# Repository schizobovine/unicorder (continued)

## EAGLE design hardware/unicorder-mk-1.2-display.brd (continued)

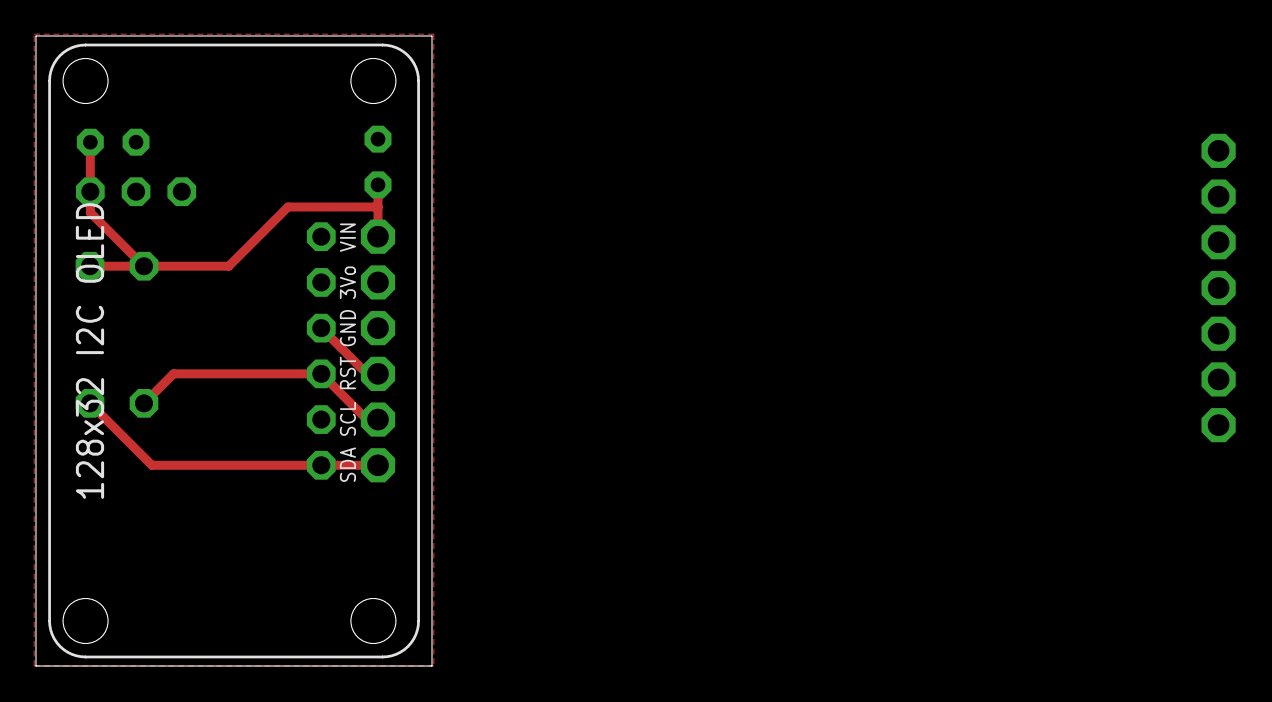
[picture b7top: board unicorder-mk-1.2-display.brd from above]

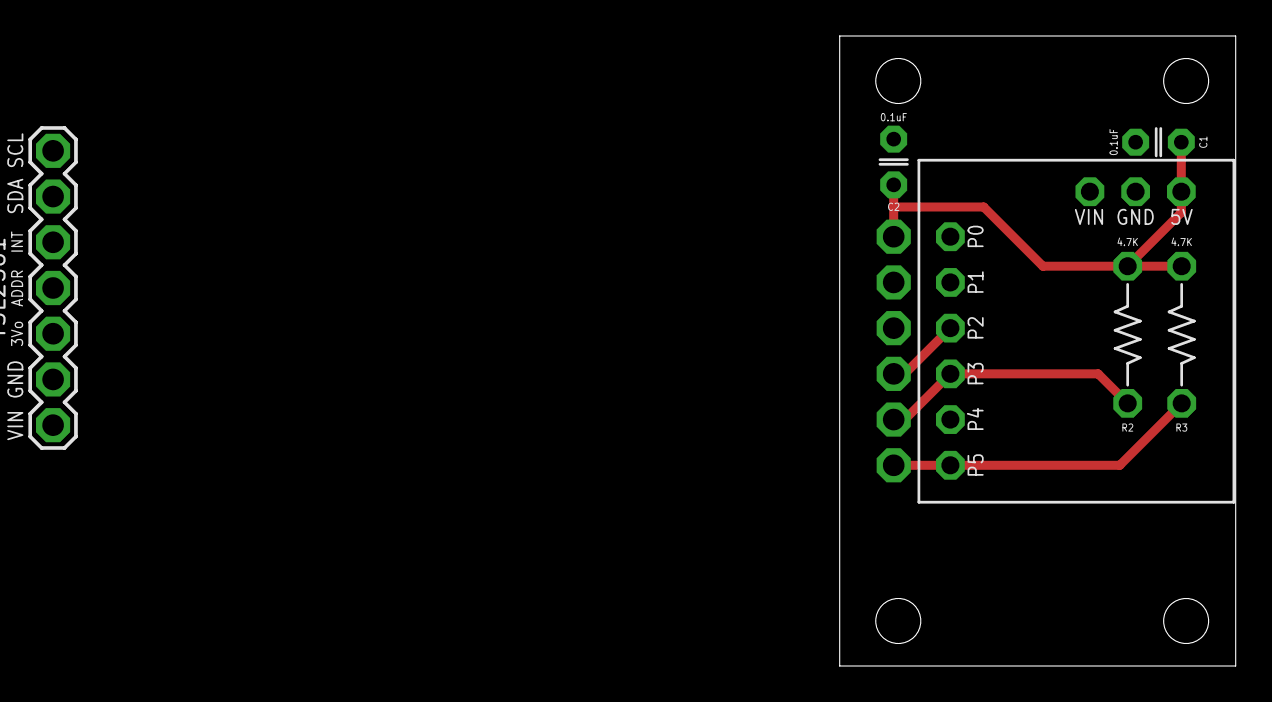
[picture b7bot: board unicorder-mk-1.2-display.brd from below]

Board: 2 copper layers, 22.0 x 35.0 mm, 8 parts (6 on the bottom side), 5 nets.

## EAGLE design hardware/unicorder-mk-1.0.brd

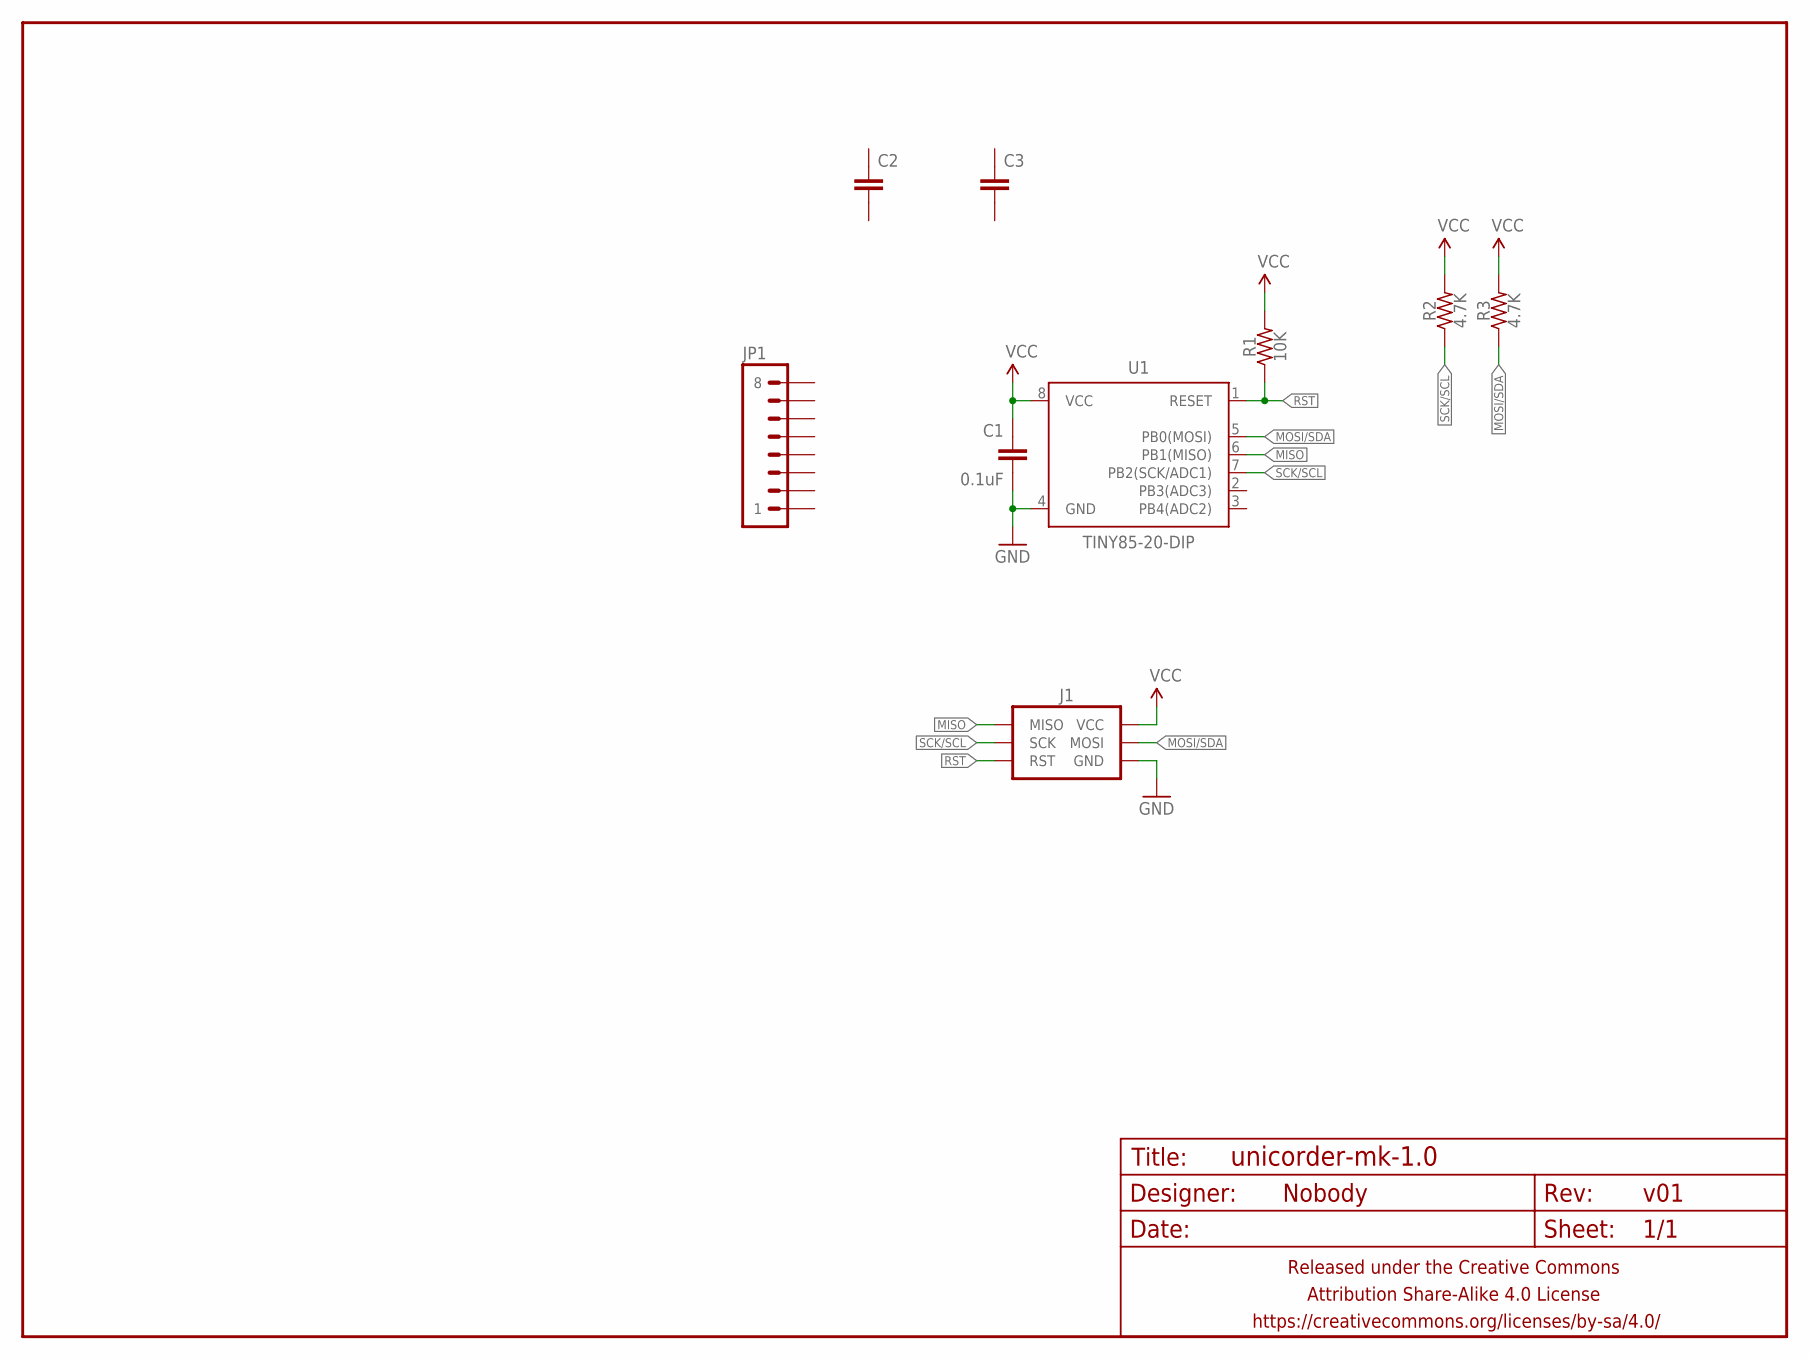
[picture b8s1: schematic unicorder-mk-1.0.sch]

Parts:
C1: 0.1uF; C025-024X044
C2, C3: CAPACITOR-CERAMIC025-024X044; C025-024X044
FRAME1: FRAME-LETTERNO_PACKAGE; DUMMY
J1: AVR_SPI_PRG_6PTH; 2X3
JP1: M081X08; 1X08
R1: 10K; RESISTOR-AXIAL-PTH-5.08MM
R2, R3: 4.7K; RESISTOR-AXIAL-PTH-5.08MM
U1: TINY85-20-DIP; DIP08

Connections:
GND: C1.2, J1.6 (GND), U1.4 (GND)
MISO: J1.1 (MISO), U1.6 (PB1(MISO))
MOSI/SDA: J1.4 (MOSI), U1.5 (PB0(MOSI))
RST: J1.5 (RST), R1.P$1 (1), U1.1 (RESET)
SCK/SCL: J1.3 (SCK), U1.7 (PB2(SCK/ADC1))
VCC: C1.1, J1.2 (VCC), R1.P$2 (2), R2.P$2 (2), R3.P$2 (2), U1.8 (VCC)

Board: 2 copper layers, 10 parts (0 on the bottom side), 6 nets, no tracks yet.

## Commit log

2015-04-27 initial skeleton commit
2015-04-28 starting board planning/layout
2015-05-07 alsdkfjkalsdf
2015-05-11 i honestly forget why
2015-06-29 i don't even remember what i was doing here
2015-08-04 thrown together temp/humidity logger
2015-08-10 timesetting script
2015-08-10 stupid program to tell me the weather inside
